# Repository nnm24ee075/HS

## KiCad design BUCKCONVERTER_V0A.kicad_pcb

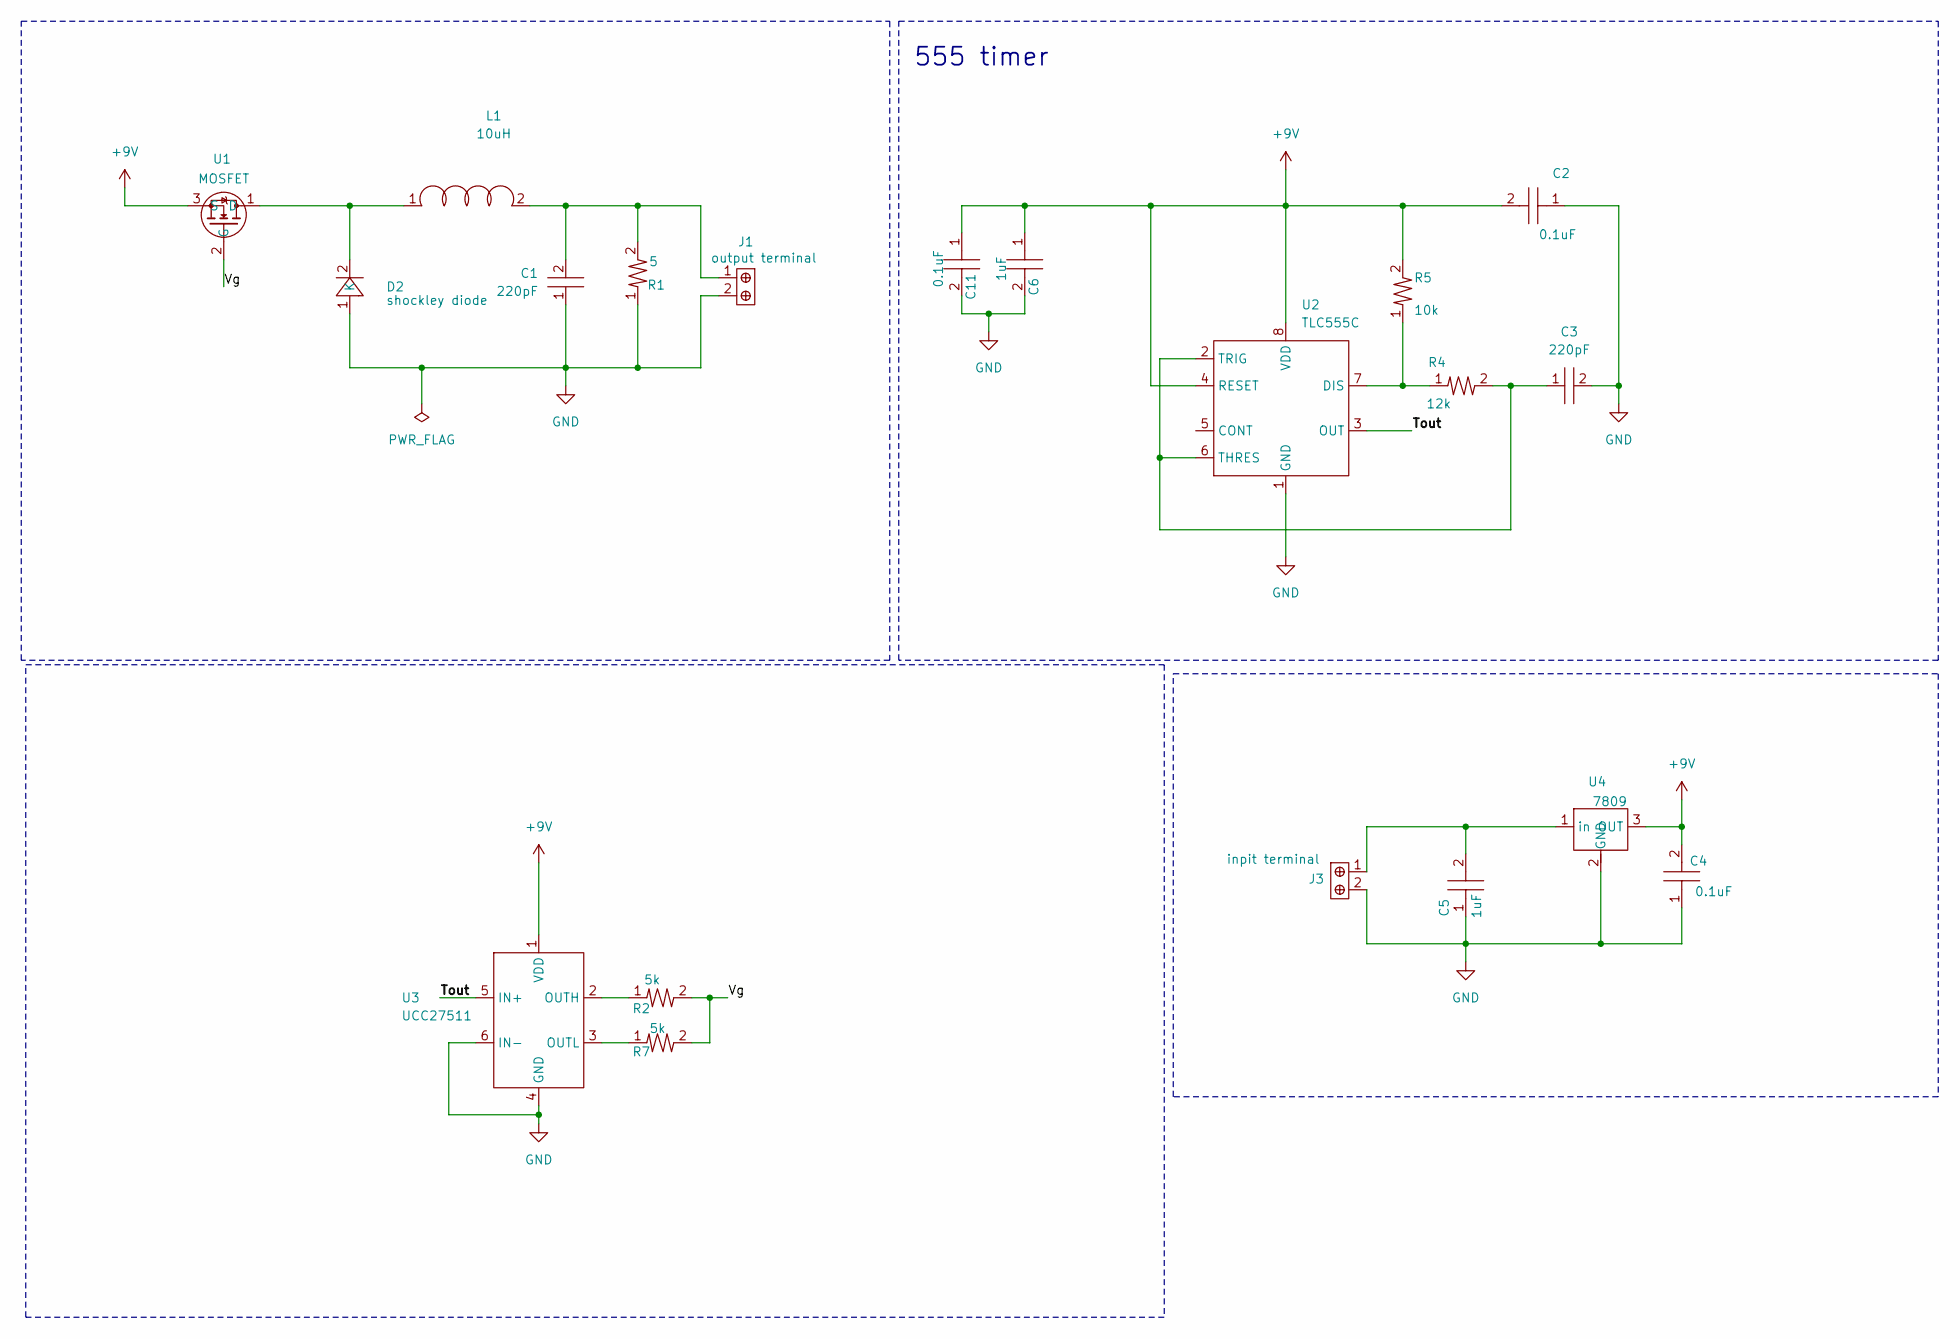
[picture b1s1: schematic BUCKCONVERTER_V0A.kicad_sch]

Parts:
C1, C3: 220pF; C0603
C2, C4: 0.1uF; C0603; MANUFACTURER PN CC0402KRX5R8BB104
C5, C6: 1uF; C0603; MANUFACTURER PN CC0603KRX5R8BB105
C11: 0.1uF; C0603; MANUFACTURER PN CC0603KRX5R8BB105
D2: shockley diode; D_0201_0603Metric
J1: output terminal; terminal_2x1
J3: inpit terminal; terminal_2x1
L1: 10uH; Inductor; Mfr. Part No L04022R7A4NTR
R1: 5; R0603; MANUFACTURER PN RPO6O3FRE0710KL
R2, R7: 5k; R0603; MANUFACTURER PN RPO6O3FRE0710KL
R4: 12k; R0603; MANUFACTURER PN RPO6O3FRE0710KL
R5: 10k; R0603; MANUFACTURER PN RPO6O3FRE0710KL
U1: MOSFET; N-Mosfet; MANUFACTURER PN NTMFS5C604NLT1G
U2: TLC555C; SOIC_8; MANUFACTURER PN TLC555CDR
U3: UCC27511; UCC; MANUFACTURER PN UCC27511DBV
U4: 7809; MANUFACTURER PN NCV78M09BDTRKG

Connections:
+9V: C2.2, C4.2, C6.1, C11.1, R5.2, U1.3 (S), U2.4 (RESET), U2.8 (VDD), U3.1 (VDD), U4.3 (OUT)
/Tout: U2.3 (OUT), U3.5 (IN+)
/Vg: R2.2, R7.2, U1.2 (G)
GND: C1.1, C2.1, C3.2, C4.1, C5.1, C6.2, C11.2, D2.1, J1.2, J3.2, R1.1, U2.1 (GND), U3.4 (GND), U3.6 (IN-), U4.2 (GND)
unnamed: C1.2, J1.1, L1.2, R1.2
unnamed: D2.2 (K), L1.1, U1.1 (D)
unnamed: R4.1, R5.1, U2.7 (DIS)
unnamed: C3.1, R4.2, U2.2 (TRIG), U2.6 (THRES)
unnamed: R2.1, U3.2 (OUTH)
unnamed: R7.1, U3.3 (OUTL)
unnamed: C5.2, J3.1, U4.1 (in)

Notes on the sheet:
555 timer

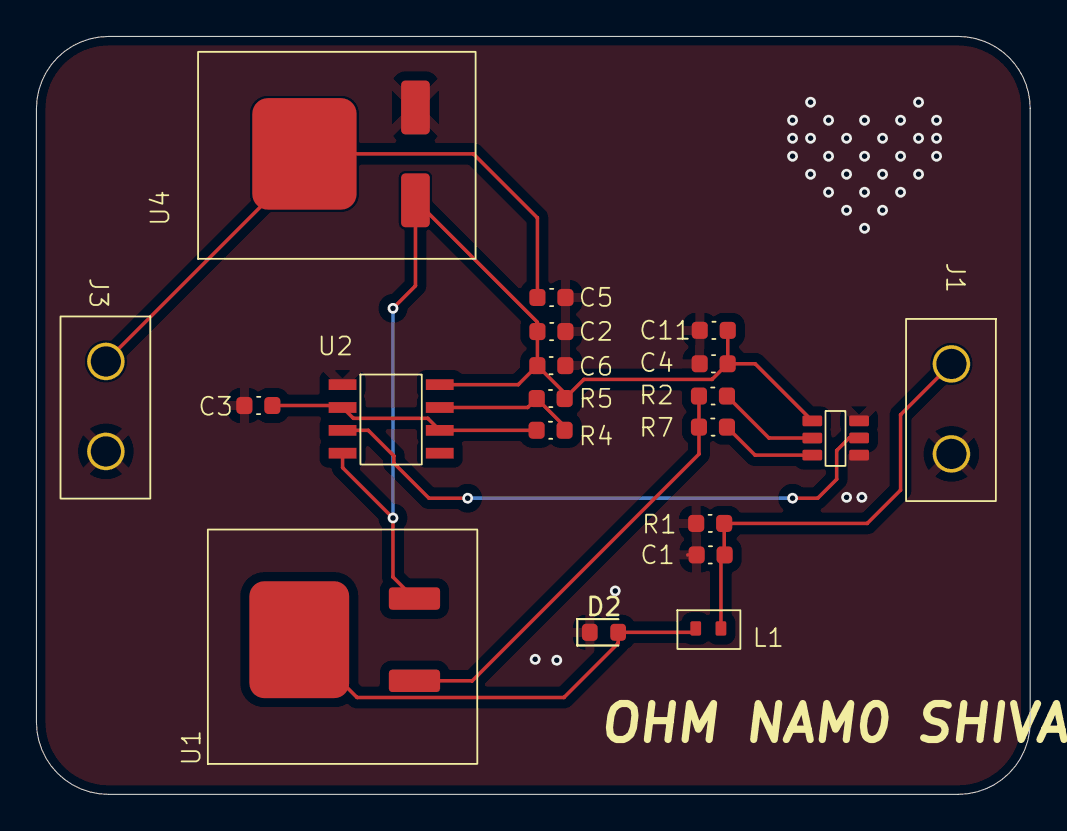
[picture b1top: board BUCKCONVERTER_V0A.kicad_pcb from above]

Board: 2 copper layers, 55.2 x 42.1 mm, 20 parts (0 on the bottom side), 11 nets.
